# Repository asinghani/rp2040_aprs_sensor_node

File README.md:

# RP2040 APRS Sensor Node

Cheap, low-power embedded sensor-node powered by an RP2040 microcontroller that communicates over the APRS (Automatic Packet Reporting System) network using the VHF Amateur Radio band.

### Features

- RP2040 microcontroller + flash memory
    - Ability to run MicroPython
- USB-C for power and programming
- JST connector for connecting to LiPo batteries
- 3V3 regulator to power microcontroller (and optionally radio)
- DRA818 VHF 1W/0.5W transceiver
    - Passive bandpass filter converts PWM output to sine-wave for transmission
    - SMA antenna connector (can use a rubber-ducky style HT antenna or an SMA cable to connect to a later antenna)
- Reset & reflash buttons, power & user LEDs
- Power-source jumpers
    - 3V3 regulator can be powered by USB or JST
    - Radio transceiver can be powered directly by JST or thru 3V3 regulator

### Photos

### Example Code

The directory `firmware` includes example code which reads from a [TMP102 temperature sensor](https://www.sparkfun.com/products/13314) and transmits over the APRS network. The pinout for the sensor is defined in `firmware/src/tmp102.c`.

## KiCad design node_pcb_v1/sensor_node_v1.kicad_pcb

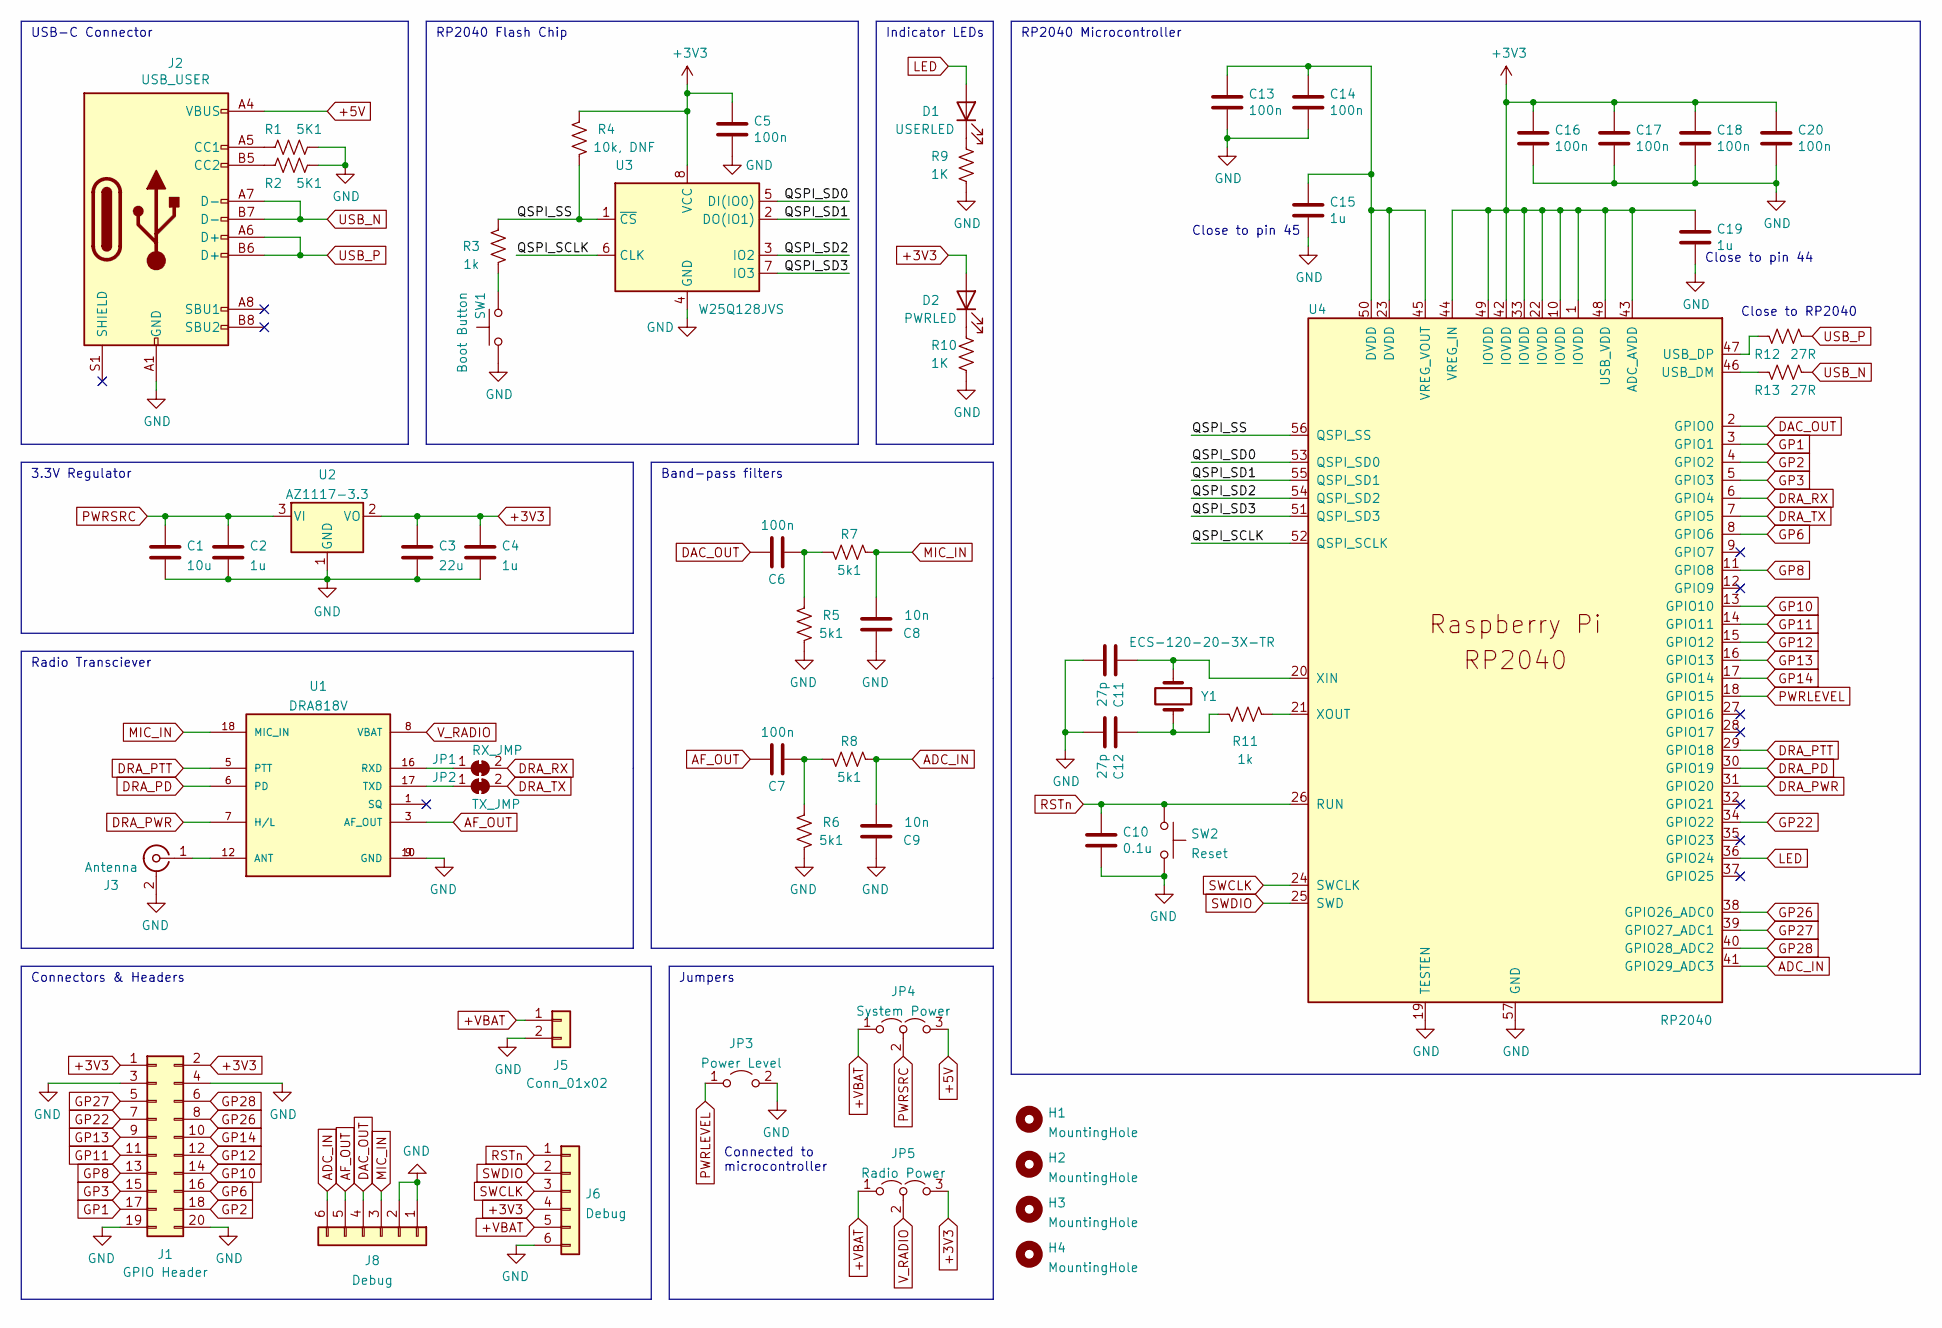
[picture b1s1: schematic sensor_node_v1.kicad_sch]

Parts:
C1: 10u; C_0603_1608Metric
C2, C4, C15, C19: 1u; C_0603_1608Metric
C3: 22u; C_0603_1608Metric
C5, C6, C7, C13, C14, C16, C17, C18, C20: 100n; C_0603_1608Metric
C8, C9: 10n; C_0603_1608Metric
C10: 0.1u; C_0603_1608Metric
C11, C12: 27p; C_0603_1608Metric
D1: USERLED; LED_0805_2012Metric
D2: PWRLED; LED_0805_2012Metric
H1, H2, H3, H4: MountingHole; MountingHole_3.2mm_M3_Pad_Via
J1: GPIO Header; PinHeader_2x10_P2.54mm_Vertical
J2: USB_USER; USB_C_HRO-31-M-12_nofront
J3: Antenna; SMA_Molex_73251-2120_EdgeMount_Horizontal
J5: Conn_01x02; JST_PH_S2B-PH-SM4-TB_1x02-1MP_P2.00mm_Horizontal
J6, J8: Debug; PinHeader_1x06_P2.54mm_Vertical
JP1: RX_JMP; SolderJumper-2_P1.3mm_Bridged_Pad1.0x1.5mm
JP2: TX_JMP; SolderJumper-2_P1.3mm_Bridged_Pad1.0x1.5mm
JP3: Power Level; PinHeader_1x02_P2.54mm_Vertical
JP4: System Power; PinHeader_1x03_P2.54mm_Vertical
JP5: Radio Power; PinHeader_1x03_P2.54mm_Vertical
R1, R2: 5K1; R_0603_1608Metric
R3, R11: 1k; R_0603_1608Metric
R4: 10k, DNF; R_0603_1608Metric
R5, R6, R7, R8: 5k1; R_0603_1608Metric
R9, R10: 1K; R_0603_1608Metric
R12, R13: 27R; R_0603_1608Metric
SW1: Boot Button; SW_SPST_PTS810
SW2: Reset; SW_SPST_PTS810
U1: DRA818V; DORJI_DRA818V; PART_REV 1.23
U2: AZ1117-3.3; SOT-223-3_TabPin2
U3: W25Q128JVS; SOIC-8_5.23x5.23mm_P1.27mm
U4: RP2040; RP2040-QFN-56
Y1: ECS-120-20-3X-TR; XTAL_ECS-120-20-3X-TR

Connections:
+3V3: C3.1, C4.1, C5.1, C16.1, C17.1, C18.1, C19.1, C20.1, D2.2 (A), J1.1, J1.2, J6.4, JP5.3 (B), R4.1, U2.2 (VO), U3.8 (VCC), U4.1 (IOVDD), U4.10 (IOVDD), U4.22 (IOVDD), U4.33 (IOVDD), U4.42 (IOVDD), U4.43 (ADC_AVDD), U4.44 (VREG_IN), U4.48 (USB_VDD), U4.49 (IOVDD)
+5V: J2.A4 (VBUS), J2.A9 (VBUS), J2.B4 (VBUS), J2.B9 (VBUS), JP4.3 (B)
+VBAT: J5.1, J6.5, JP4.1 (A), JP5.1 (A)
/QSPI_SCLK: U3.6 (CLK), U4.52 (QSPI_SCLK)
/QSPI_SD0: U3.5 (DI(IO0)), U4.53 (QSPI_SD0)
/QSPI_SD1: U3.2 (DO(IO1)), U4.55 (QSPI_SD1)
/QSPI_SD2: U3.3 (IO2), U4.54 (QSPI_SD2)
/QSPI_SD3: U3.7 (IO3), U4.51 (QSPI_SD3)
/QSPI_SS: R3.2, R4.2, U3.1 (~CS), U4.56 (QSPI_SS)
ADC_IN: C9.2, J8.6, R8.2, U4.41 (GPIO29_ADC3)
AF_OUT: C7.1, J8.5, U1.3 (AF_OUT)
DAC_OUT: C6.1, J8.4, U4.2 (GPIO0)
DRA_PD: U1.6 (PD), U4.30 (GPIO19)
DRA_PTT: U1.5 (PTT), U4.29 (GPIO18)
DRA_PWR: U1.7 (H/L), U4.31 (GPIO20)
DRA_RX: JP1.2 (B), U4.6 (GPIO4)
DRA_TX: JP2.2 (B), U4.7 (GPIO5)
GND: C1.2, C2.2, C3.2, C4.2, C5.2, C8.1, C9.1, C10.2, C11.2, C12.2, C13.2, C14.2, C15.2, C16.2, C17.2, C18.2, C19.2, C20.2, J1.3, J1.4, J1.19, J1.20, J2.A1 (GND), J2.A12 (GND), J2.B1 (GND), J2.B12 (GND), J3.2 (Ext), J5.2, J6.6, J8.1, J8.2, JP3.2 (B), R1.2, R2.2, R5.2, R6.2, R9.2, R10.2, SW1.1, SW2.2, U1.9 (GND), U1.10 (GND), U2.1 (GND), U3.4 (GND), U4.19 (TESTEN), U4.57 (GND)
GP1: J1.17, U4.3 (GPIO1)
GP2: J1.18, U4.4 (GPIO2)
GP3: J1.15, U4.5 (GPIO3)
GP6: J1.16, U4.8 (GPIO6)
GP8: J1.13, U4.11 (GPIO8)
GP10: J1.14, U4.13 (GPIO10)
GP11: J1.11, U4.14 (GPIO11)
GP12: J1.12, U4.15 (GPIO12)
GP13: J1.9, U4.16 (GPIO13)
GP14: J1.10, U4.17 (GPIO14)
GP22: J1.7, U4.34 (GPIO22)
GP26: J1.8, U4.38 (GPIO26_ADC0)
GP27: J1.5, U4.39 (GPIO27_ADC1)
GP28: J1.6, U4.40 (GPIO28_ADC2)
LED: D1.2 (A), U4.36 (GPIO24)
MIC_IN: C8.2, J8.3, R7.2, U1.18 (MIC_IN)
unnamed: C6.2, R5.1, R7.1
unnamed: C7.2, R6.1, R8.1
unnamed: C11.1, U4.20 (XIN), Y1.1
unnamed: C12.1, R11.2, Y1.2
unnamed: C13.1, C14.1, C15.1, U4.23 (DVDD), U4.45 (VREG_VOUT), U4.50 (DVDD)
unnamed: D1.1 (K), R9.1
unnamed: D2.1 (K), R10.1
unnamed: J2.A5 (CC1), R1.1
unnamed: J2.B5 (CC2), R2.1
unnamed: J3.1 (In), U1.12 (ANT)
unnamed: JP1.1 (A), U1.16 (RXD)
unnamed: JP2.1 (A), U1.17 (TXD)
unnamed: R3.1, SW1.2
unnamed: R11.1, U4.21 (XOUT)
unnamed: R12.2, U4.47 (USB_DP)
unnamed: R13.2, U4.46 (USB_DM)
PWRLEVEL: JP3.1 (A), U4.18 (GPIO15)
PWRSRC: C1.1, C2.1, JP4.2 (C), U2.3 (VI)
RSTn: C10.1, J6.1, SW2.1, U4.26 (RUN)
SWCLK: J6.3, U4.24 (SWCLK)
SWDIO: J6.2, U4.25 (SWD)
USB_N: J2.A7 (D-), J2.B7 (D-), R13.1
USB_P: J2.A6 (D+), J2.B6 (D+), R12.1
V_RADIO: JP5.2 (C), U1.8 (VBAT)

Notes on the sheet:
RP2040 Microcontroller
USB-C Connector
3.3V Regulator
Radio Transciever
Jumpers
RP2040 Flash Chip
Connected to microcontroller
Connectors & Headers
Band-pass filters
Indicator LEDs
Close to pin 44
Close to RP2040
Close to pin 45

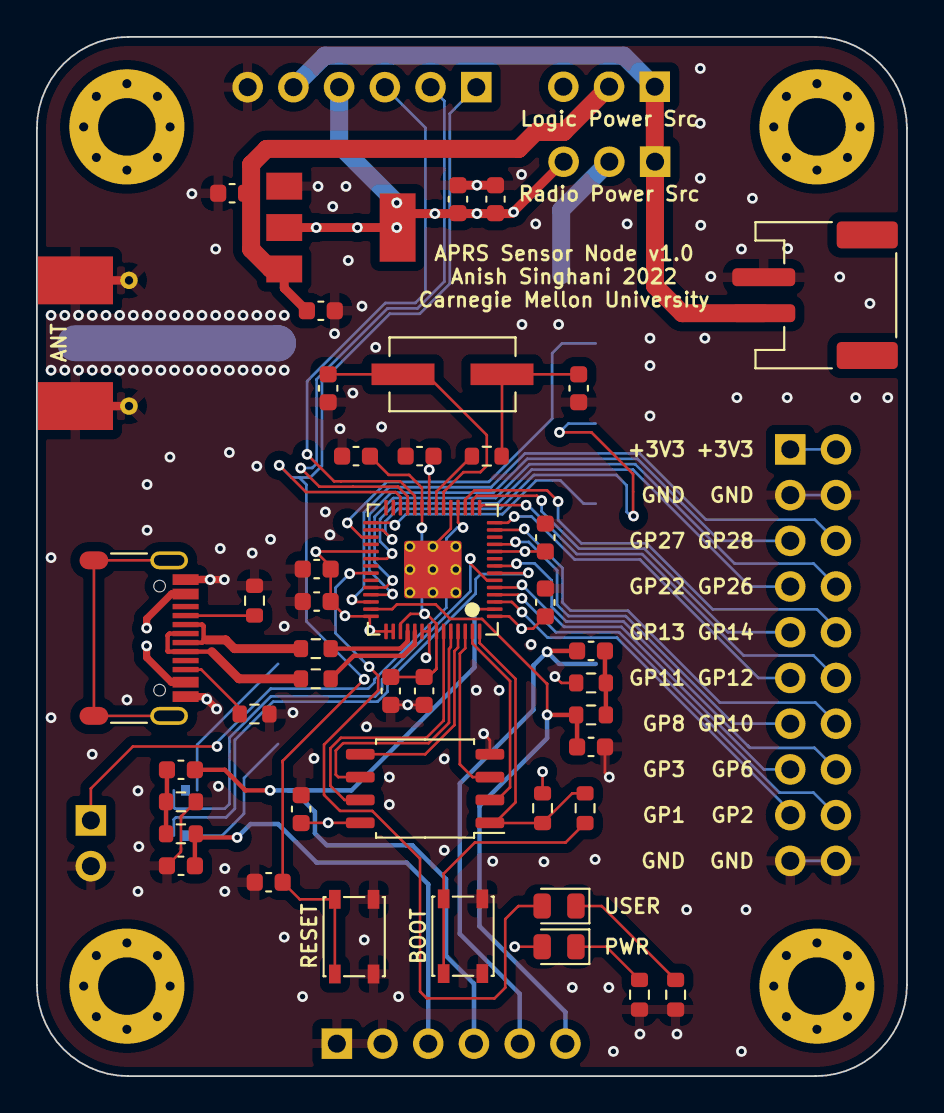
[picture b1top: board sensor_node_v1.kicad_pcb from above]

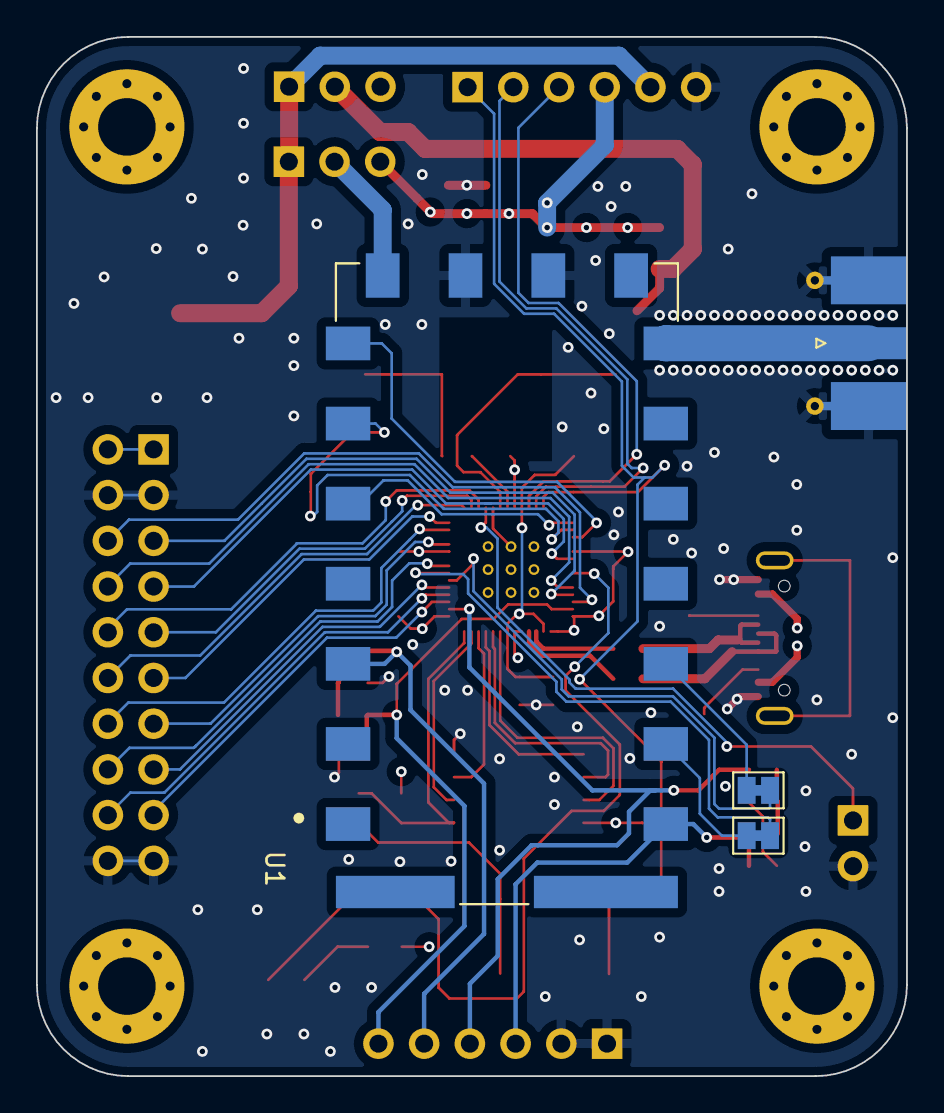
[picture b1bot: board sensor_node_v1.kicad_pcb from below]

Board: 4 copper layers, 48.3 x 57.7 mm, 57 parts (4 on the bottom side), 58 nets.

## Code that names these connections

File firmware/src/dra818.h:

#include <stdbool.h>

#define DRA_RX 4
#define DRA_TX 5

#define DRA_PTT 18
#define DRA_PD 19
#define DRA_PWR 20

void dra818_init_aprs();
void dra818_set_lowpower(bool low_power);

void dra818_key(bool transmit);

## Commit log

2022-04-22 Initial commit, import kicad project
2022-04-27 Add example firmware
2022-04-27 Add note about callsign
2022-04-30 Add README
